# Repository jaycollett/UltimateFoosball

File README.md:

# UltimateFoosball

Cool lights and sound add-in for my son's foosball table.

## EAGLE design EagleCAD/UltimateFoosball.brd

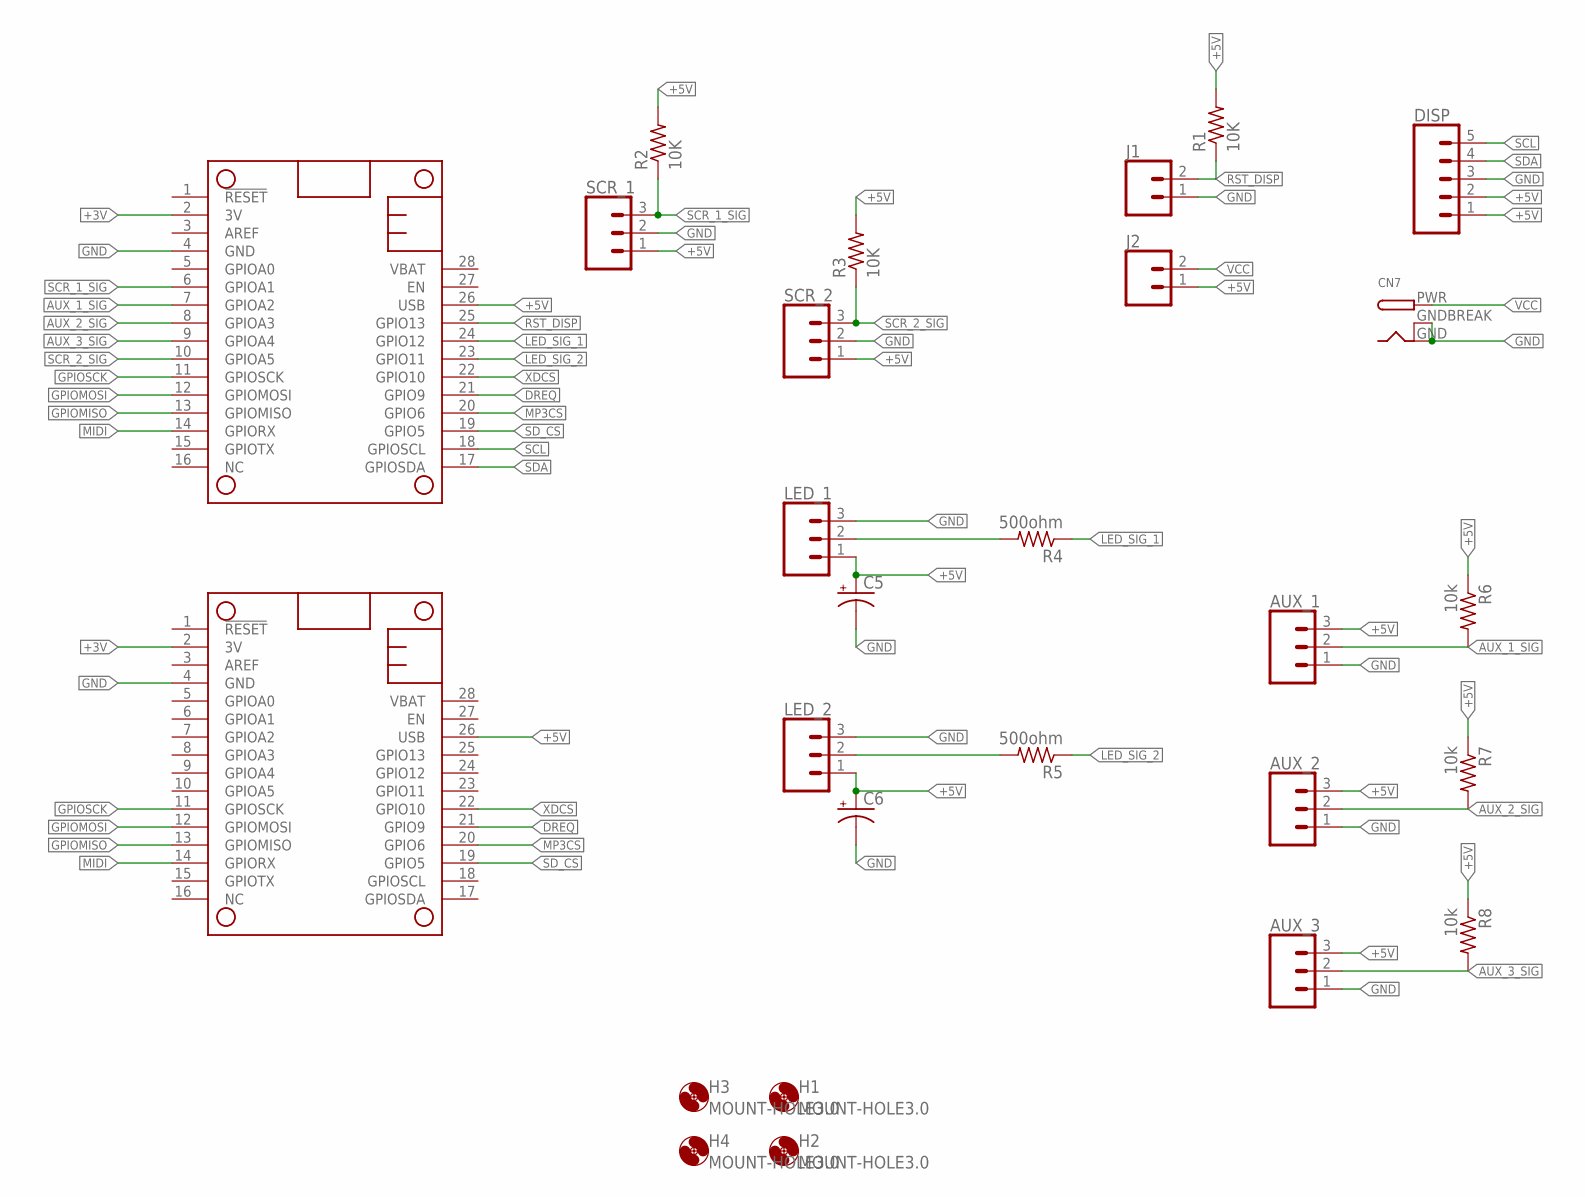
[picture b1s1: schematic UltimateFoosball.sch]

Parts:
AUX_1, AUX_2, AUX_3: CONN_03; 1X03
C5, C6: CPOL-USE5-13; E5-13
CN7: DCBARRELPTH; DCJACK_2MM_PTH
DISP: CONN_05; 1X05
H1, H2, H3, H4: MOUNT-HOLE3.0; 3,0
J1, J2: CONN_02PTH3; 1X02_LONGPADS
LED_1, LED_2: CONN_03; 1X03
MS1: FEATHERWING_NODIM; FEATHERWING_DIM
MUSIC_WING: FEATHERWING_NODIM; FEATHERWING_DIM
R1, R2, R3: 10K; 0309/12
R4, R5: 500ohm; 0309/12
R6, R7, R8: 10k; 0309/12
SCR_1, SCR_2: CONN_03; 1X03

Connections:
+3V: MS1.2 (3V), MUSIC_WING.2 (3V)
+5V: AUX_1.3, AUX_2.3, AUX_3.3, C5.+, C6.+, DISP.1, DISP.2, J2.1, LED_1.1, LED_2.1, MS1.26 (USB), MUSIC_WING.26 (USB), R1.2, R2.2, R3.2, R6.1, R7.1, R8.1, SCR_1.1, SCR_2.1
AUX_1_SIG: AUX_1.2, MS1.7 (GPIOA2), R6.2
AUX_2_SIG: AUX_2.2, MS1.8 (GPIOA3), R7.2
AUX_3_SIG: AUX_3.2, MS1.9 (GPIOA4), R8.2
DREQ: MS1.21 (GPIO9), MUSIC_WING.21 (GPIO9)
GND: AUX_1.1, AUX_2.1, AUX_3.1, C5.-, C6.-, CN7.GND, CN7.GNDBREAK, DISP.3, J1.1, LED_1.3, LED_2.3, MS1.4 (GND), MUSIC_WING.4 (GND), SCR_1.2, SCR_2.2
GPIOMISO: MS1.13 (GPIOMISO), MUSIC_WING.13 (GPIOMISO)
GPIOMOSI: MS1.12 (GPIOMOSI), MUSIC_WING.12 (GPIOMOSI)
GPIOSCK: MS1.11 (GPIOSCK), MUSIC_WING.11 (GPIOSCK)
LED_SIG_1: MS1.24 (GPIO12), R4.1
LED_SIG_2: MS1.23 (GPIO11), R5.1
MIDI: MS1.14 (GPIORX), MUSIC_WING.14 (GPIORX)
MP3CS: MS1.20 (GPIO6), MUSIC_WING.20 (GPIO6)
unnamed: LED_1.2, R4.2
unnamed: LED_2.2, R5.2
RST_DISP: J1.2, MS1.25 (GPIO13), R1.1
SCL: DISP.5, MS1.18 (GPIOSCL)
SCR_1_SIG: MS1.6 (GPIOA1), R2.1, SCR_1.3
SCR_2_SIG: MS1.10 (GPIOA5), R3.1, SCR_2.3
SDA: DISP.4, MS1.17 (GPIOSDA)
SD_CS: MS1.19 (GPIO5), MUSIC_WING.19 (GPIO5)
VCC: CN7.PWR, J2.2
XDCS: MS1.22 (GPIO10), MUSIC_WING.22 (GPIO10)

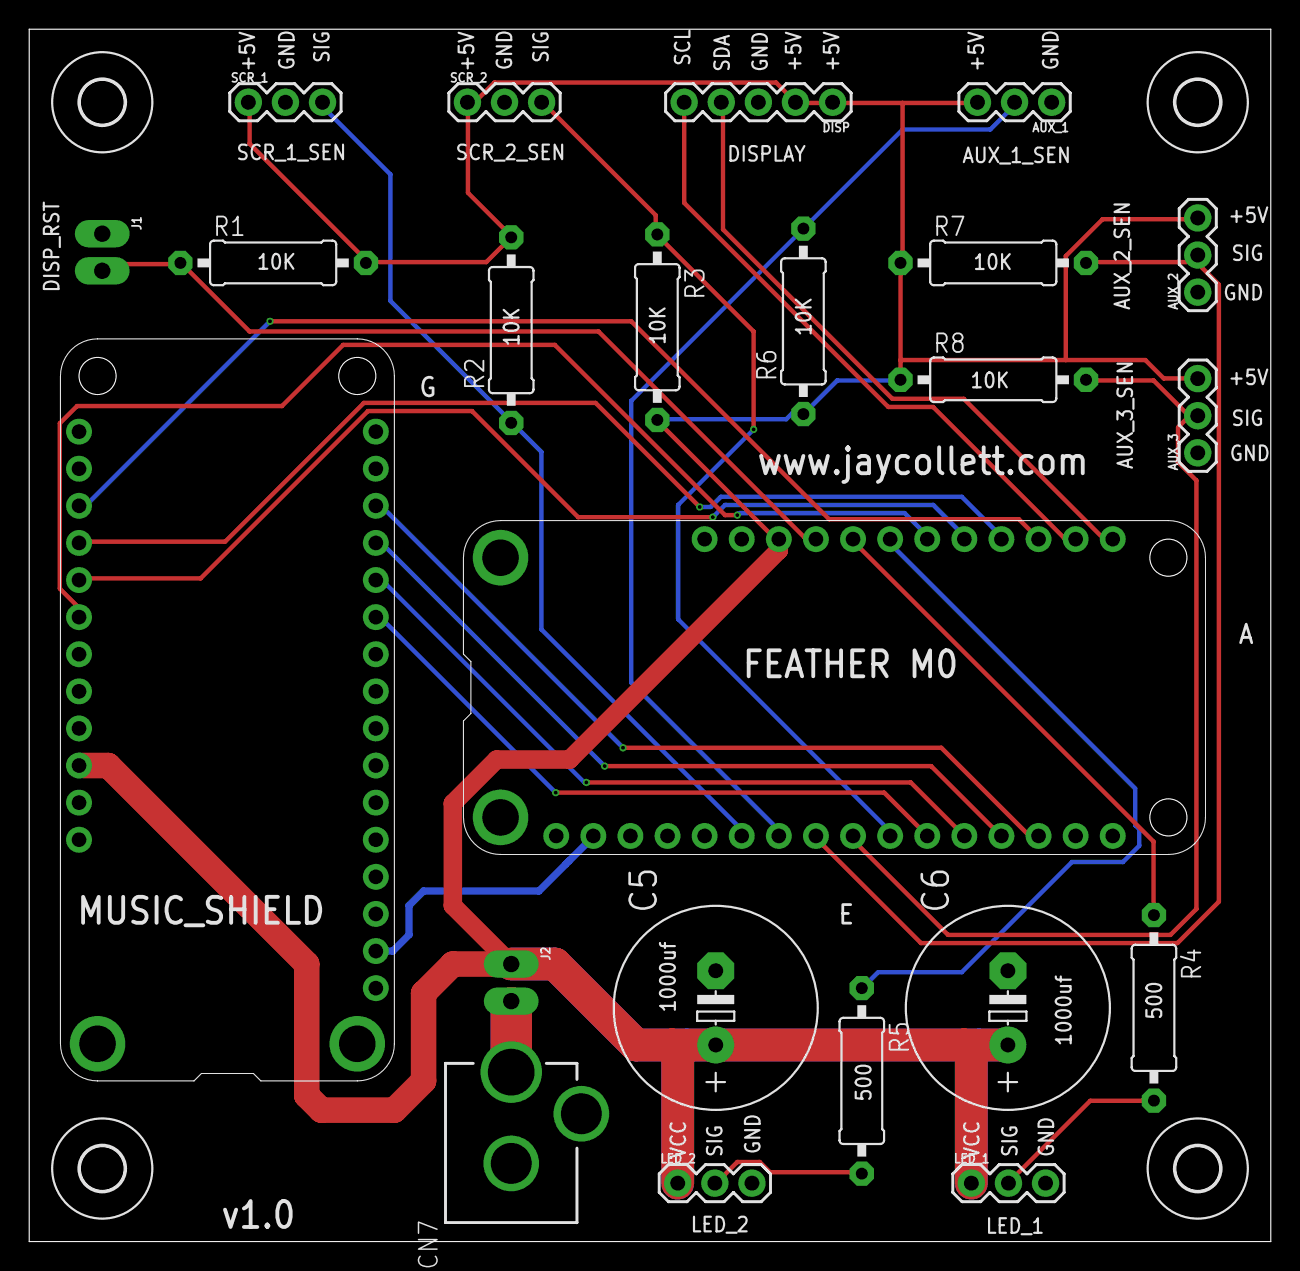
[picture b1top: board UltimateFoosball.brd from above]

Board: 2 copper layers, 85.0 x 83.0 mm, 27 parts (0 on the bottom side), 24 nets.

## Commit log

2019-12-02 initial board and schematic for foosball controller...
2019-12-02 Version 1 complete, sent to OSHPark
2019-12-10 Add firmware file(s), initial commit of firmware
2019-12-11 adding some sound clips to project
2019-12-11 building audio folder structure
2019-12-11 Fist pass of all sound playing logic, added more sounds
2019-12-13 Update code that calls the playfile method with char buff
2019-12-18 fix bored time and small tweak to clearing display
2019-12-18 adding first set of basic animations for home and visiting team scores
2019-12-19 fix ISR functions with use of loop method and general debug of version 1
2019-12-20 code refactoring
2019-12-23 Add logic to stop music/sound if it's playing...
2019-12-24 added game over sounds/logic and update order of scoreboard updating
2019-12-25 update version number
2019-12-25 add a few more score and hot sounds
2019-12-25 tweak light show length and fix issue with reset and gameover
2019-12-25 fix issue with swapped audio on game win
2021-01-09 Create support for travis ci and update readme

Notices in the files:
parts and their libraries:
SparkFun-Connectors: Licensing: Creative Commons ShareAlike 4.0 International - https://creativecommons.org/licenses/by-sa/4.0
